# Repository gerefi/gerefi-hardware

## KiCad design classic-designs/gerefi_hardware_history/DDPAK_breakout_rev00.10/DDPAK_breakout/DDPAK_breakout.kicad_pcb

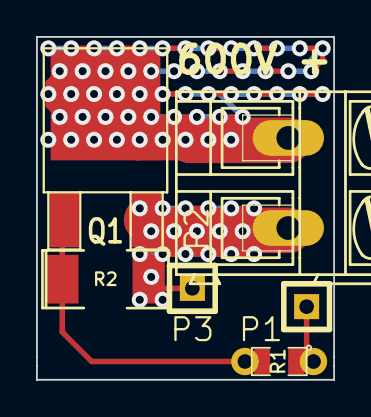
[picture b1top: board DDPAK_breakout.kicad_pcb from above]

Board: 2 copper layers, 16.5 x 19.1 mm, 6 parts (0 on the bottom side), 4 nets.

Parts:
P1, P3: CONN_1; SIL-1
P2: CONN_2; AK300-2
Q1: IRGS14C40L; DPAK2
R1: 1K; SM0805_jumper
R2: 100K; SM2010

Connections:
/GND: P2.2, P3.1, Q1.3, R2.2
/HV: P2.1, Q1.2
/SIG: P1.1, R1.1
/SIG2: Q1.1, R1.2, R2.1

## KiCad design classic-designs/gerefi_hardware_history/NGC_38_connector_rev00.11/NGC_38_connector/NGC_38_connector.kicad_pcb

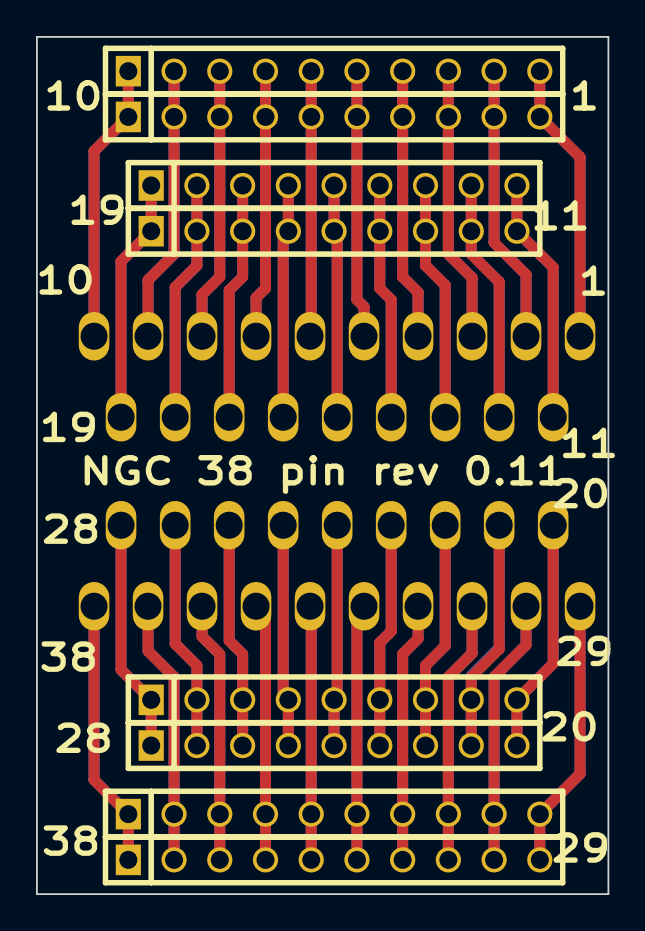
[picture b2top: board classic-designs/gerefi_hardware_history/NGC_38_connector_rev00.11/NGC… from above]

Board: 2 copper layers, 31.8 x 47.6 mm, 9 parts (0 on the bottom side), 38 nets.

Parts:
P1: DIL38; PCM_C1
P2, P4, P6, P9: CONN_10; SIL-10
P3, P5, P7, P8: CONN_9; SIL-9

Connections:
unnamed: P1.1, P2.1, P6.1
unnamed: P1.2, P2.2, P6.2
unnamed: P1.3, P2.3, P6.3
unnamed: P1.4, P2.4, P6.4
unnamed: P1.5, P2.5, P6.5
unnamed: P1.6, P2.6, P6.6
unnamed: P1.7, P2.7, P6.7
unnamed: P1.8, P2.8, P6.8
unnamed: P1.9, P2.9, P6.9
unnamed: P1.10, P2.10, P6.10
unnamed: P1.17, P3.7, P7.7
unnamed: P1.24, P5.5, P8.5
unnamed: P1.25, P5.6, P8.6
unnamed: P1.26, P5.7, P8.7
unnamed: P1.27, P5.8, P8.8
unnamed: P1.28, P5.9, P8.9
unnamed: P1.11, P3.1, P7.1
unnamed: P1.12, P3.2, P7.2
unnamed: P1.13, P3.3, P7.3
unnamed: P1.14, P3.4, P7.4
unnamed: P1.15, P3.5, P7.5
unnamed: P1.16, P3.6, P7.6
unnamed: P1.23, P5.4, P8.4
unnamed: P1.18, P3.8, P7.8
unnamed: P1.19, P3.9, P7.9
unnamed: P1.31, P4.3, P9.3
unnamed: P1.29, P4.1, P9.1
unnamed: P1.30, P4.2, P9.2
unnamed: P1.32, P4.4, P9.4
unnamed: P1.33, P4.5, P9.5
unnamed: P1.34, P4.6, P9.6
unnamed: P1.35, P4.7, P9.7
unnamed: P1.36, P4.8, P9.8
unnamed: P1.37, P4.9, P9.9
unnamed: P1.38, P4.10, P9.10
unnamed: P1.20, P5.1, P8.1
unnamed: P1.21, P5.2, P8.2
unnamed: P1.22, P5.3, P8.3

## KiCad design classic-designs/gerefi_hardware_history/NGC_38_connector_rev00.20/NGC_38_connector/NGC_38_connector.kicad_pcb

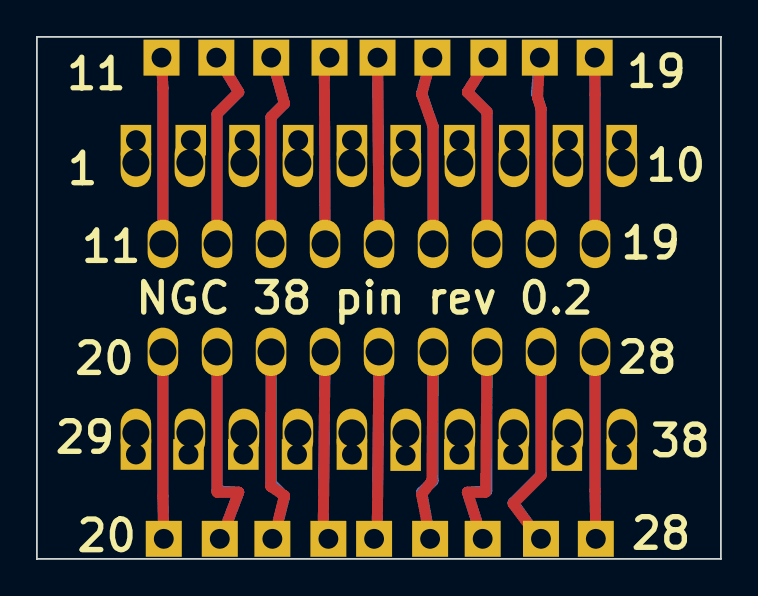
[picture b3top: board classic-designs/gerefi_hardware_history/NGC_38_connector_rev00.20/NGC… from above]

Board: 2 copper layers, 38.0 x 29.0 mm, 5 parts (0 on the bottom side), 38 nets.

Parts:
P1: DIL38; PCM_C1
P2, P4: CONN_10; SIL-10
P3, P5: CONN_9; SIL-9

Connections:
unnamed: P1.15, P3.5
unnamed: P1.10, P2.10
unnamed: P1.9, P2.9
unnamed: P1.8, P2.8
unnamed: P1.7, P2.7
unnamed: P1.6, P2.6
unnamed: P1.5, P2.5
unnamed: P1.4, P2.4
unnamed: P1.3, P2.3
unnamed: P1.2, P2.2
unnamed: P1.1, P2.1
unnamed: P1.19, P3.9
unnamed: P1.18, P3.8
unnamed: P1.17, P3.7
unnamed: P1.16, P3.6
unnamed: P1.20, P5.1
unnamed: P1.14, P3.4
unnamed: P1.13, P3.3
unnamed: P1.12, P3.2
unnamed: P1.11, P3.1
unnamed: P1.28, P5.9
unnamed: P1.27, P5.8
unnamed: P1.26, P5.7
unnamed: P1.25, P5.6
unnamed: P1.24, P5.5
unnamed: P1.23, P5.4
unnamed: P1.22, P5.3
unnamed: P1.21, P5.2
unnamed: P1.31, P4.3
unnamed: P1.34, P4.6
unnamed: P1.33, P4.5
unnamed: P1.32, P4.4
unnamed: P1.38, P4.10
unnamed: P1.30, P4.2
unnamed: P1.29, P4.1
unnamed: P1.37, P4.9
unnamed: P1.36, P4.8
unnamed: P1.35, P4.7

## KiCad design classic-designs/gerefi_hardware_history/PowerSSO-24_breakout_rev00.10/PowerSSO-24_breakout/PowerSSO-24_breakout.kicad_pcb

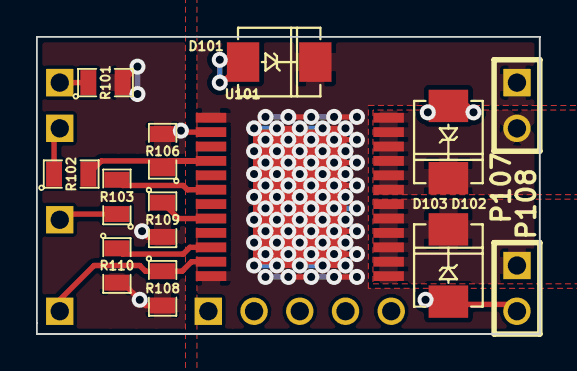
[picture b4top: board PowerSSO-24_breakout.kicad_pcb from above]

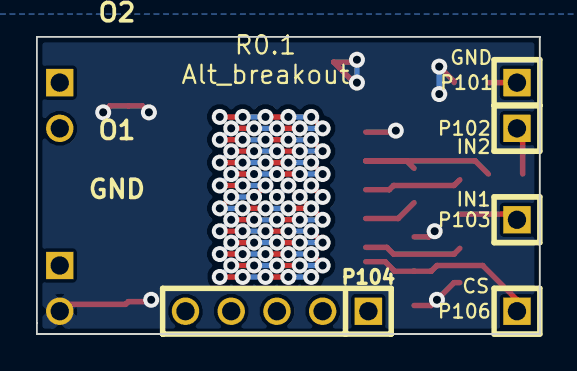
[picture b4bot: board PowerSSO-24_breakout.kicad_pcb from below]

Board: 2 copper layers, 27.9 x 16.5 mm, 18 parts (5 on the bottom side), 12 nets.

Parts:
D101, D102, D103: P6SMB36AT3G; DO-214AA(SMB)
P101, P102, P103, P106: CONN_1; SIL-1
P104: CONN_5; SIL-5
P107, P108: CONN_2; SIL-2
R101: TBD; SM0805
R102, R103, R106, R108: 10K; SM0805
R109, R110: 1K; SM0805
U101: VND5E025AKTR; PowerSSO-24

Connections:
/CS_DIS: P106.1, R108.1, U101.11
/I1: R109.1, U101.8
/I2: R110.1, U101.10
/IN1: R103.2, U101.6
/IN2: R102.2, R106.1, U101.4
/O1: D103.2, P108.1, U101.13, U101.14, U101.15, U101.16, U101.17, U101.18
/O2: D102.2, P107.2, U101.19, U101.20, U101.21, U101.22, U101.23, U101.24
/VCC: D101.2, P107.1, U101.1, U101.12, U101.EXP
GND: D101.1, D102.1, D103.1, P108.2, R101.2, R106.2, R108.2, R109.2, R110.2, U101.2
unnamed: P101.1, R101.1
unnamed: P103.1, R103.1
unnamed: P102.1, R102.1

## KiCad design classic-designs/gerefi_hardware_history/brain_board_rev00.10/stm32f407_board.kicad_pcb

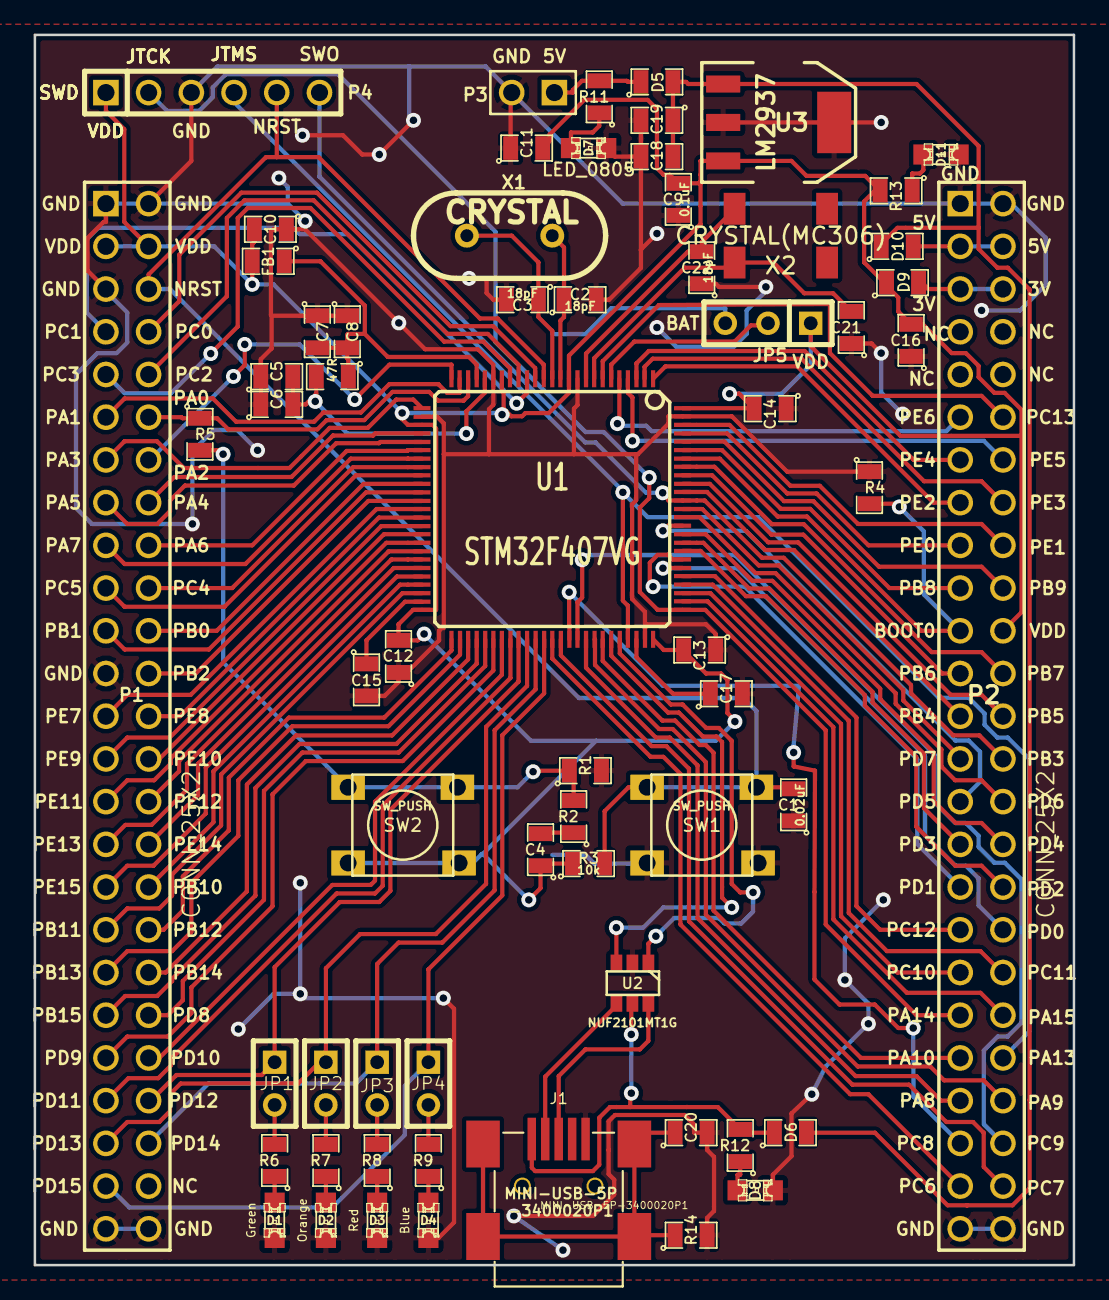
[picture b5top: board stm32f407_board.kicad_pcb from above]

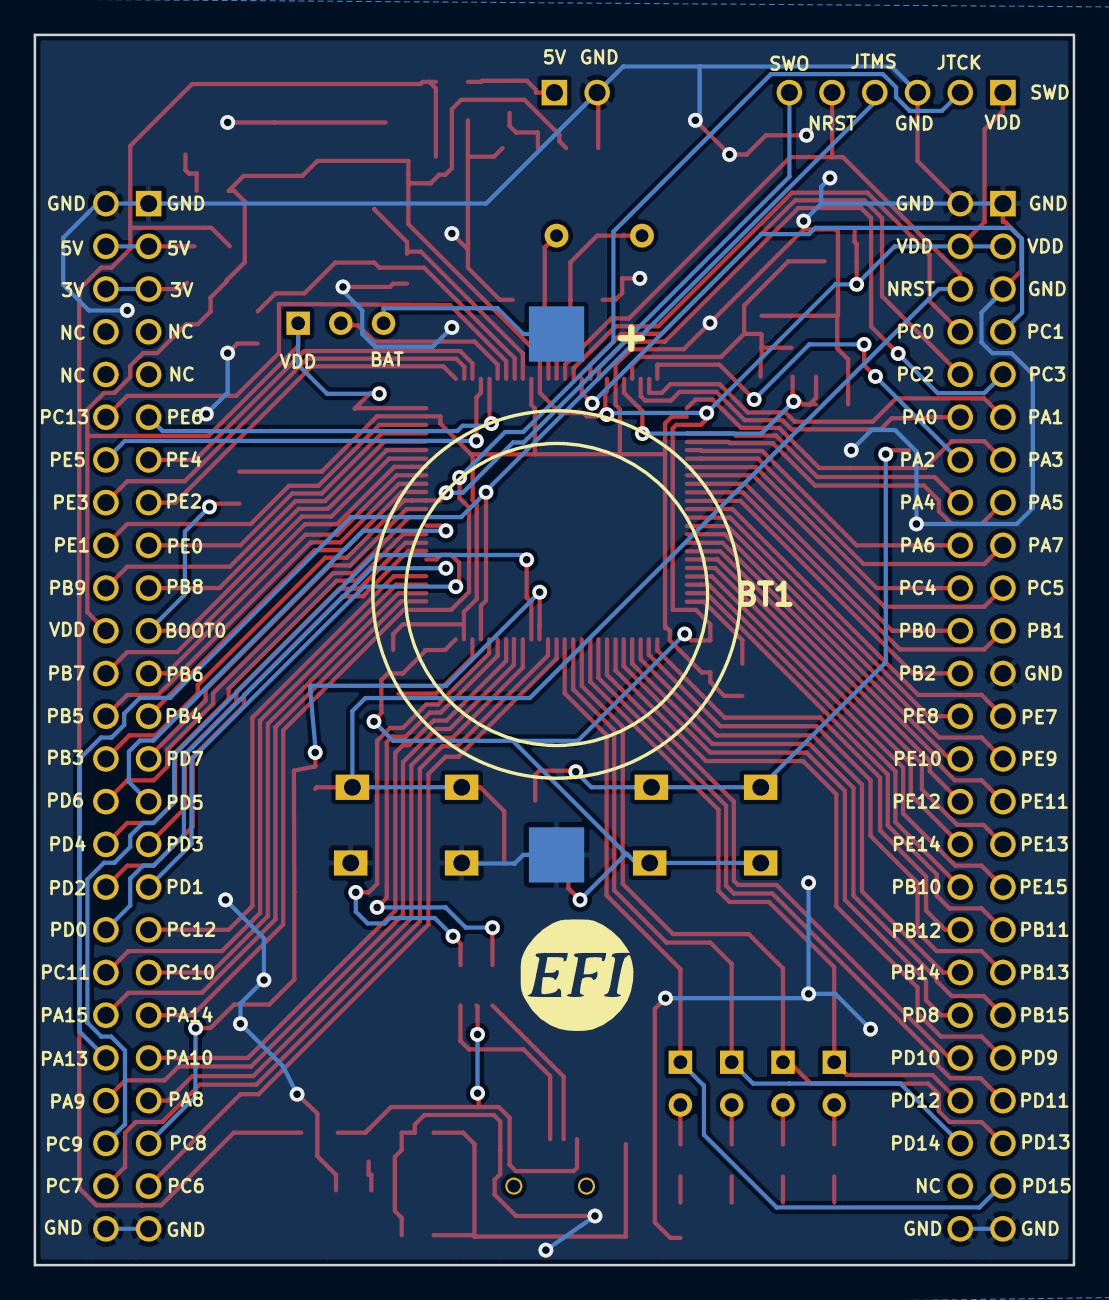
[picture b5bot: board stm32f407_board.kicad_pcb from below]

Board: 2 copper layers, 61.8 x 73.2 mm, 67 parts (2 on the bottom side), 113 nets.

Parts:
BT1: BATTERY_CR2032; BATT_CR2032_MPD
C1: 0.02uF; SM0805
C2, C3, C21, C22: 18pF; SM0805
C4, C15, C17: 2u2F; SM0805
C5, C8: 0.01uF; SM0805
C6, C7, C16: 1uF; SM0805
C9, C10, C11, C12, C13, C14, C18, C20: 0.1uF; SM0805
C19: 4.7uF; SM0805
D1, D2, D3, D4, D7, D8, D11: LED_0805; LED-0805_A
D5, D6, D9, D10: DIODESCH; SM0805
FB1: FILTER; SM0805
G1: LOGO; LOGO_F
J1: MINI-USB-5P-3400020P1
JP1, JP2, JP3, JP4: JUMPER; JUMPER-2
JP5: JUMPER3; SIL-3
P1, P2: CONN_25X2; PIN_ARRAY_25x2_A
P3: CONN_2; PIN_ARRAY_2_A
P4: CONN_6; PIN_ARRAY-6X1
R1, R3, R4: 10k; SM0805
R2: 100R; SM0805
R5: 330R; SM0805
R6, R7, R8, R9: 680R; SM0805
R10: 47R; SM0805
R11, R12, R13: 1k; SM0805
R14: 100k; SM0805
SW1, SW2: SW_PUSH; TL-1105
U1: STM32F407VG; TQFP_100
U2: NUF2101MT1G; SOT-457
U3: LM2937; SOT223
X1: CRYSTAL; HC-49V
X2: CRYSTAL(MC306); MC-306

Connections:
/3V: D9.2, P2.5, P2.6
/5V: D10.2, P2.3, P2.4
/5Vi: C18.2, C19.1, D5.2, D6.2, D10.1, U3.1
/BOOT0: P2.21, R4.2, U1.94
/D+: J1.3, U2.6
/D-: J1.2, U2.4
/NRST: C1.2, P1.6, P4.5, R3.2, SW1.1, U1.14
/PA0: P1.12, R5.1, U1.23
/PA1: P1.11, U1.24
/PA2: P1.14, U1.25
/PA3: P1.13, U1.26
/PA4: P1.16, U1.29
/PA5: P1.15, U1.30
/PA6: P1.18, U1.31
/PA7: P1.17, U1.32
/PA8: P2.43, U1.67
/PA9: P2.44, U1.68
/PA10: P2.41, U1.69
/PA11: U1.70, U2.3
/PA12: U1.71, U2.1
/PA13: P2.42, P4.4, U1.72
/PA14: P2.39, P4.2, U1.76
/PA15: P2.40, U1.77
/PB0: P1.22, U1.35
/PB1: P1.21, U1.36
/PB2: P1.24, U1.37
/PB3: P2.28, P4.6, U1.89
/PB4: P2.25, U1.90
/PB5: P2.26, U1.91
/PB6: P2.23, U1.92
/PB7: P2.24, U1.93
/PB8: P2.19, U1.95
/PB9: P2.20, U1.96
/PB10: P1.34, U1.47
/PB11: P1.35, U1.48
/PB12: P1.36, U1.51
/PB13: P1.37, U1.52
/PB14: P1.38, U1.53
/PB15: P1.39, U1.54
/PC0: P1.8, U1.15
/PC1: P1.7, U1.16
/PC2: P1.10, U1.17
/PC3: P1.9, U1.18
/PC4: P1.20, U1.33
/PC5: P1.19, U1.34
/PC6: P2.47, U1.63
/PC7: P2.48, U1.64
/PC8: P2.45, U1.65
/PC9: P2.46, U1.66
/PC10: P2.37, U1.78
/PC11: P2.38, U1.79
/PC12: P2.35, U1.80
/PC13: P2.12, U1.7
/PD0: P2.36, U1.81
/PD1: P2.33, U1.82
/PD2: P2.34, U1.83
/PD3: P2.31, U1.84
/PD4: P2.32, U1.85
/PD5: P2.29, U1.86
/PD6: P2.30, U1.87
/PD7: P2.27, U1.88
/PD8: P1.40, U1.55
/PD9: P1.41, U1.56
/PD10: P1.42, U1.57
/PD11: P1.43, U1.58
/PD12: JP1.1, P1.44, U1.59
/PD13: JP2.1, P1.45, U1.60
/PD14: JP3.1, P1.46, U1.61
/PD15: JP4.1, P1.47, U1.62
/PE0: P2.17, U1.97
/PE1: P2.18, U1.98
/PE2: P2.15, U1.1
/PE3: P2.16, U1.2
/PE4: P2.13, U1.3
/PE5: P2.14, U1.4
/PE6: P2.11, U1.5
/PE7: P1.25, U1.38
/PE8: P1.26, U1.39
/PE9: P1.27, U1.40
/PE10: P1.28, U1.41
/PE11: P1.29, U1.42
/PE12: P1.30, U1.43
/PE13: P1.31, U1.44
/PE14: P1.32, U1.45
/PE15: P1.33, U1.46
/VDD: C4.1, C9.2, C10.2, C11.2, C12.2, C13.2, C14.2, C16.2, D9.1, FB1.2, JP5.1, P1.3, P1.4, P2.22, P4.1, R3.1, R13.2, SW2.2, U1.11, U1.19, U1.28, U1.50, U1.75, U1.100, U3.3
/Vbus: D6.1, J1.1, R12.2, U2.5
GND: BT1.2, C1.1, C2.2, C3.2, C5.1, C6.1, C7.1, C8.1, C9.1, C10.1, C11.1, C12.1, C13.1, C14.1, C15.2, C16.1, C17.2, C18.1, C19.2, C20.2, C21.1, C22.1, D1.2, D2.2, D3.2, D4.2, D7.2, D8.2, D11.2, J1.5, P1.1, P1.2, P1.5, P1.23, P1.49, P1.50, P2.1, P2.2, P2.49, P2.50, P3.2, P4.3, R1.2, R4.1, R14.2, SW1.2, U1.10, U1.20, U1.27, U1.74, U1.99, U2.2, U3.2, U3.4
unnamed: JP5.2, U1.6
unnamed: BT1.1, JP5.3
unnamed: C4.2, R2.1
unnamed: R1.1, R2.2, R5.2, SW2.1
unnamed: JP1.2, R6.2
unnamed: JP2.2, R7.2
unnamed: JP3.2, R8.2
unnamed: JP4.2, R9.2
unnamed: D7.1, R11.1
unnamed: D5.1, P3.1, R11.2
unnamed: D8.1, R12.1
unnamed: D1.1, R6.1
unnamed: D2.1, R7.1
unnamed: D3.1, R8.1
unnamed: D4.1, R9.1
unnamed: D11.1, R13.1
unnamed: C20.1, J1.6, R14.1
unnamed: C5.2, C6.2, R10.2, U1.21
unnamed: C21.2, U1.8, X2.1
unnamed: C22.2, U1.9, X2.4
unnamed: C3.1, U1.13, X1.1
unnamed: C17.1, U1.73
unnamed: C2.1, U1.12, X1.2
unnamed: C15.1, U1.49
unnamed: C7.2, C8.2, FB1.1, R10.1, U1.22

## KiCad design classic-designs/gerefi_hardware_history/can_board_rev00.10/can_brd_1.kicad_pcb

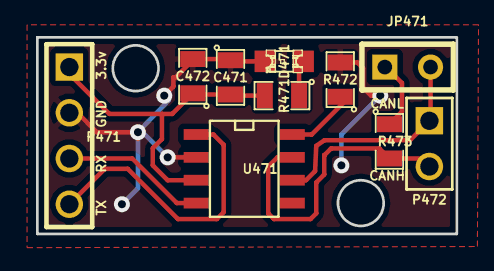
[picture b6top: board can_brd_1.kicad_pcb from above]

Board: 2 copper layers, 23.3 x 10.9 mm, 11 parts (1 on the bottom side), 9 nets.

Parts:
C471: .1uF; SM0805
C472: 4.7uF; SM0805
D471: RED; LED-0805
G471: LOGO; LOGO_F
JP471: JUMPER; SIL-2
P471: CONN_4; PIN_ARRAY_4x1
P472: CONN_2; PIN_ARRAY_2_A
R471: 1k; SM0805
R472: 10k; SM0805
R473: 120; SM0805
U471: SN65HVD230; SO8E

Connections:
/3.3V: C471.2, C472.1, P471.1, R471.2, U471.3
/CANH: P472.2, R473.2, U471.7
/CANL: JP471.2, P472.1, U471.6
/CAN_RX: P471.3, U471.4
/CAN_TX: P471.4, U471.1
GND: C471.1, C472.2, D471.2, P471.2, R472.2, U471.2
unnamed: R472.1, U471.8
unnamed: JP471.1, R473.1
unnamed: D471.1, R471.1
